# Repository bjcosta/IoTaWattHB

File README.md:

# IoTaWattHB
IoTaWatt Homebrew is a repository for experimentation with new ideas against the official IoTaWatt project developed by Bob Lemaire (https://github.com/boblemaire/IoTaWatt).

This repository brings all 3rd party dependencies required to build IoTaWatt into a single folder for simple archiving/backup using git submodules. The commands to manage the submodules may differ with your version of git

-------
Purpose

I am using this project as a means to experiment with electronic and embedded design. I dont expect all the things I am going to try will work out.

The IoTaWatt project works quite well as it is. However after playing with it a little, I decided I would like a few extra features and so this has given me a good project to run with. The main improvements I want to experiment with from base IotaWatt include:
* Add POST support for the pvoutput.org website
* Single voltage transformer for both powering the IoTaWatt and sampling the mains voltage
* Pulse monitoring for monitoring electrcial smart meters, gas and water mains
* Add push-button switch for manual interaction like resetting connected WiFi AP
* Use accurate V-ref as both a reference but also to provide the BIAS so software doesn't have to "guess" the DC offset
* Add support for temperature and humidity sensor
* Use more accurate sampling technique (simultaneous/continuous sampling)

A key problem that I came across in this work, is that the existing ESP8266 NodeMCU has very few available GPIO lines and IoTaWatt already uses them all.

A real solution for this problem is moving to an ESP32 based board. Based on his comments in forums, this is in the future plans for Bob. I wanted to have my changes work with close to stock IoTaWatt so if I choose in the future I can revert back to stock firmware. For this reason, I decided to try and creatively work around the GPIO limitation (inspired by official IoTaWatts usage of GPIO for the status LED) and keep using the ESP8266.

Building
--------

When building this project, I defined the following base locations. You can use whatever you like for these.

IOTAWATTHB_HOME=$HOME/dev/IoTaWattHB
ARDUINO_HOME=$IOTAWATTHB_HOME/arduino-1.8.5/

Checkout Source
---------------

First checkout the IoTaWattHB project
* mkdir $HOME/dev && cd $HOME/dev
* git clone ssh://git@github.com/bjcosta/IoTaWattHB.git

Then you need to pull in the 3rd party git submodules
* cd $IOTAWATTHB_HOME
* git submodule update --init --recursive

The repository uses a symlink to bring in Crypto library from arduinolibs. If you are building on windows, you will need to set up a manual junction:
** cd %IOTAWATTHB_HOME%\deps\libraries
** del Crypto
** mklink /j Crypto ..\arduinolibs\libraries\Crypto
** git update-index --assume-unchanged Crypto

Install Arduino IDE
-------------------

* https://www.arduino.cc/en/Main/Software (Used version 1.8.5)
* Extract the file to: ${ARDUINO_HOME}
** tar -xvJf arduino-1.8.5-linux64.tar.xz -C $IOTAWATTHB_HOME/
* cd ${ARDUINO_HOME} && ./arduino
* Change sketchbook location Menu: File -> Preferences
** Set Sketchbook location to: ${IOTAWATTHB_HOME}/deps
** I like to setup so that everything we depend on is in the projects folder so I can track versions for this project and return to it long in the future if I need to. Arduino is not great for this, but it is possible by changing your sketchbook location. Remember to restore it if you are working on other projects once you are finished with this one. 
** By doing this we can archive everything together (all 3rd party dependencies along with the module) and back it up.

Install ESP8266 dev tools
-------------------------

* http://esp8266.github.io/Arduino/versions/2.0.0/doc/installing.html
* The git submodule containing the dev tools has already been cloned under ${IOTAWATTHB_HOME}/deps/hardware/esp8266com/esp8266
* We still however need to download the necessary binaries for cross compiling
** cd ${IOTAWATTHB_HOME}/deps/hardware/esp8266com/esp8266/tools
** python get.py

Now compile the sketch
----------------------

* cd ${ARDUINO_HOME} && ./arduino
* Menu: File -> Open : ${IOTAWATTHB_HOME}/IoTaWatt/Firmware/IotaWatt/IotaWatt.ino
* Menu: Tools -> Board -> NodeMCU 1.0 (ESP-12E Module)
** Note: The 1.0 board is the one I was using, also known as 
* Menu: Sketch -> Verify/Compile

TODO
----

* Document setting up Exception decoder for Arduino ESP https://github.com/me-no-dev/EspExceptionDecoder
* Document setup of VisualMicro Visual Studio plugin http://www.visualmicro.com
* Document installation of FTDI drivers for Windows
** http://www.ftdichip.com/Drivers/VCP.htm
** http://www.ftdichip.com/Drivers/CDM/CDM%20v2.12.28%20WHQL%20Certified.zip
** http://www.ftdichip.com/Drivers/CDM/CDM21228_Setup.zip
* Document steps to upload and run a sketch

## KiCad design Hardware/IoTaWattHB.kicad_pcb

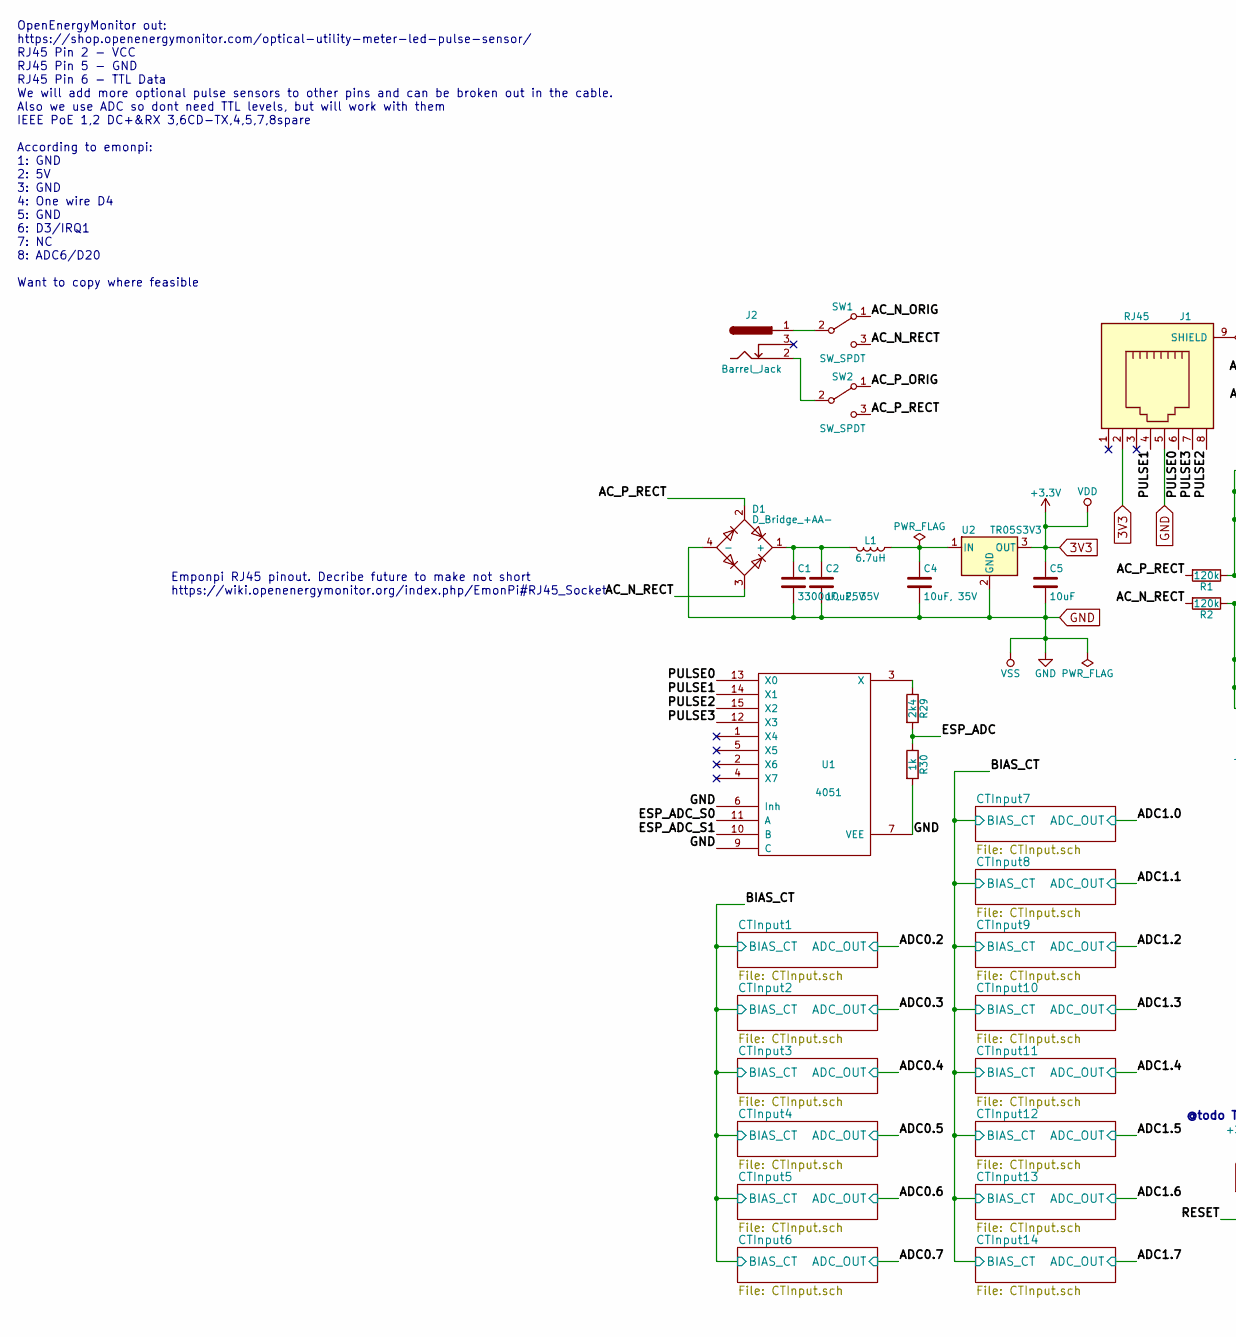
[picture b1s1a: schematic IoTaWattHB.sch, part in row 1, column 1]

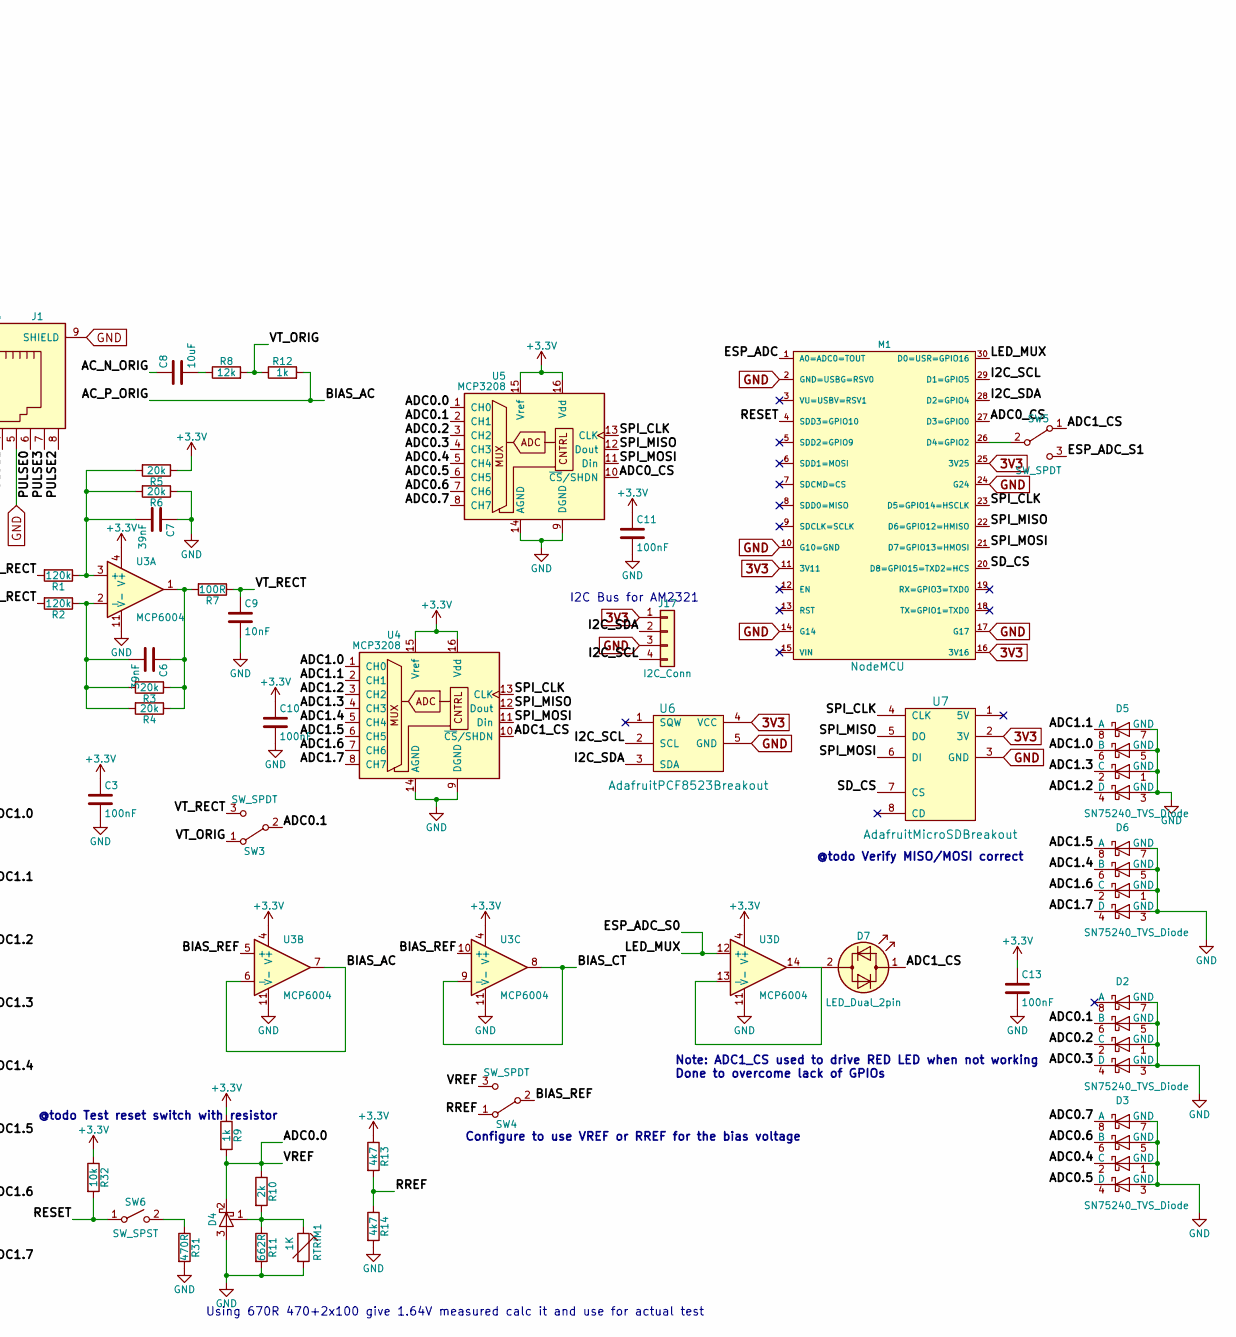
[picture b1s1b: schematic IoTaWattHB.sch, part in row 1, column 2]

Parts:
C1: 3300uF, 25V; CP_Radial_D16.0mm_P7.50mm
C2, C4: 10uF, 35V; CP_Radial_D5.0mm_P2.00mm
C3, C10, C11, C13: 100nF; C_Rect_L18.0mm_W5.0mm_P15.00mm_FKS3_FKP3
C5, C8: 10uF; CP_Radial_D5.0mm_P2.00mm
C6, C7: 39nF; C_Rect_L18.0mm_W5.0mm_P15.00mm_FKS3_FKP3
C9: 10nF; C_Disc_D12.5mm_W5.0mm_P7.50mm
D1: D_Bridge_+AA-; Diode_Bridge_14.5x3.5
D2, D3, D5, D6: SN75240_TVS_Diode; DIP-8_W7.62mm
D4: AdjustableShuntVoltageReference; TO-92_Inline_Narrow_Oval
D7: LED_Dual_2pin; LED_D5.0mm_Horizontal_O1.27mm_Z9.0mm
J1: RJ45; RJ45_TycoElectric_Side_8Pos
J2: Barrel_Jack; DC_RSPRO_2.1
J17: I2C_Conn; Socket_Strip_Straight_1x04_Pitch2.54mm
L1: 6.7uH; L_Axial_L16.0mm_D6.3mm_P7.62mm_Vertical_Fastron_VHBCC
M1: NodeMCU; NodeMCU_notracks
R1, R2: 120k; R_Axial_DIN0309_L9.0mm_D3.2mm_P15.24mm_Horizontal
R3, R4, R5, R6: 20k; R_Axial_DIN0309_L9.0mm_D3.2mm_P15.24mm_Horizontal
R7: 100R; R_Axial_DIN0309_L9.0mm_D3.2mm_P15.24mm_Horizontal
R8: 12k; R_Axial_DIN0309_L9.0mm_D3.2mm_P15.24mm_Horizontal
R9, R12, R30: 1k; R_Axial_DIN0309_L9.0mm_D3.2mm_P15.24mm_Horizontal
R10: 2k; R_Axial_DIN0309_L9.0mm_D3.2mm_P15.24mm_Horizontal
R11: 662R; R_Axial_DIN0309_L9.0mm_D3.2mm_P15.24mm_Horizontal
R13, R14: 4k7; R_Axial_DIN0309_L9.0mm_D3.2mm_P15.24mm_Horizontal
R29: 2k4; R_Axial_DIN0309_L9.0mm_D3.2mm_P15.24mm_Horizontal
R31: 470R; R_Axial_DIN0309_L9.0mm_D3.2mm_P15.24mm_Horizontal
R32: 10k; R_Axial_DIN0309_L9.0mm_D3.2mm_P15.24mm_Horizontal
RTRIM1: 1K; Potentiometer_Trimmer_ACP_CA9h5_Vertical_Px5.0mm_Py5.0mm
SW1, SW2, SW3, SW4, SW5: SW_SPDT; Pin_Header_Straight_1x03_Pitch2.54mm
SW6: SW_SPST; SW_SPST_Angled_9233WW
U1: 4051; DIP-16_W7.62mm
U2: TR05S3V3; TO-220-3_Vertical_or_SIP-3T
U3: MCP6004; DIP-14_W7.62mm
U4, U5: MCP3208; SOIC-16_ADAPTER_3.9x9.9mm_Pitch1.27mm_notracks
U6: AdafruitPCF8523Breakout
U7: AdafruitMicroSDBreakout

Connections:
3V3: C3.1, C5.1, C10.1, C11.1, C13.1, J1.2, J17.1, M1.11 (3V11), M1.16 (3V16), M1.25 (3V25), R5.1, R9.1, R13.1, R32.1, U1.16 (VDD), U2.3 (OUT), U3.4 (V+), U4.15 (Vref), U4.16 (Vdd), U5.15 (Vref), U5.16 (Vdd), U6.4 (VCC), U7.2 (3V)
/AC_N_ORIG: C8.1, SW1.1 (A)
/AC_N_RECT: D1.3, R2.2, SW1.3 (C)
/AC_P_ORIG: R12.2, SW2.1 (A), U3.6 (-), U3.7
/AC_P_RECT: D1.2, R1.2, SW2.3 (C)
/ADC0.0: D4.2 (K), R9.2, R10.1, SW4.3 (C), U5.1 (CH0)
/ADC0.1: D2.6 (B), SW3.2 (B), U5.2 (CH1)
/ADC0.2: D2.2 (C), U5.3 (CH2); also elsewhere on the board
/ADC0.3: D2.4 (D), U5.4 (CH3); also elsewhere on the board
/ADC0.4: D3.2 (C), U5.5 (CH4); also elsewhere on the board
/ADC0.5: D3.4 (D), U5.6 (CH5); also elsewhere on the board
/ADC0.6: D3.6 (B), U5.7 (CH6); also elsewhere on the board
/ADC0.7: D3.8 (A), U5.8 (CH7); also elsewhere on the board
/ADC0_CS: M1.27 (D3=GPIO0), U5.10 (~CS~/SHDN)
/ADC1.0: D5.6 (B), U4.1 (CH0); also elsewhere on the board
/ADC1.1: D5.8 (A), U4.2 (CH1); also elsewhere on the board
/ADC1.2: D5.4 (D), U4.3 (CH2); also elsewhere on the board
/ADC1.3: D5.2 (C), U4.4 (CH3); also elsewhere on the board
/ADC1.4: D6.6 (B), U4.5 (CH4); also elsewhere on the board
/ADC1.5: D6.8 (A), U4.6 (CH5); also elsewhere on the board
/ADC1.6: D6.2 (C), U4.7 (CH6); also elsewhere on the board
/ADC1.7: D6.4 (D), U4.8 (CH7); also elsewhere on the board
/ADC1_CS: D7.1 (KA), SW5.1 (A), U4.10 (~CS~/SHDN)
/BIAS_CT: U3.8, U3.9 (-); also elsewhere on the board
/BIAS_REF: SW4.2 (B), U3.5 (+), U3.10 (+)
/ESP_ADC: M1.1 (A0=ADC0=TOUT), R29.2, R30.1
/ESP_ADC_S0: M1.30 (D0=USR=GPIO16), U1.11 (A), U3.12 (+)
/ESP_ADC_S1: SW5.3 (C), U1.10 (B)
/I2C_SCL: J17.4, M1.29 (D1=GPIO5), U6.2 (SCL)
/I2C_SDA: J17.2, M1.28 (D2=GPIO4), U6.3 (SDA)
/PULSE0: J1.6, U1.13 (X0)
/PULSE1: J1.4, U1.14 (X1)
/PULSE2: J1.8, U1.15 (X2)
/PULSE3: J1.7, U1.12 (X3)
/RESET: M1.4 (SDD3=GPIO10), R32.2, SW6.1 (A)
/RREF: R13.2, R14.1, SW4.1 (A)
/SD_CS: M1.20 (D8=GPIO15=TXD2=HCS), U7.7 (CS)
/SPI_CLK: M1.23 (D5=GPIO14=HSCLK), U4.13 (CLK), U5.13 (CLK), U7.4 (CLK)
/SPI_MISO: M1.22 (D6=GPIO12=HMISO), U4.12 (Dout), U5.12 (Dout), U7.5 (DO)
/SPI_MOSI: M1.21 (D7=GPIO13=HMOSI), U4.11 (Din), U5.11 (Din), U7.6 (DI)
/VT_ORIG: R8.2, R12.1, SW3.1 (A)
/VT_RECT: C9.1, R7.1, SW3.3 (C)
GND: C1.2, C2.2, C3.2, C4.2, C5.2, C7.1, C9.2, C10.2, C11.2, C13.2, D1.4 (-), D2.1 (GND), D2.3 (GND), D2.5 (GND), D2.7 (GND), D3.1 (GND), D3.3 (GND), D3.5 (GND), D3.7 (GND), D4.3 (A), D5.1 (GND), D5.3 (GND), D5.5 (GND), D5.7 (GND), D6.1 (GND), D6.3 (GND), D6.5 (GND), D6.7 (GND), J1.5, J1.9 (SHIELD), J17.3, M1.2 (GND=USBG=RSV0), M1.10 (G10=GND), M1.14 (G14), M1.17 (G17), M1.24 (G24), R6.1, R11.2, R14.2, R30.2, R31.2, RTRIM1.2, U1.6 (Inh), U1.7 (VEE), U1.8 (VSS), U1.9 (C), U2.2 (GND), U3.11 (V-), U4.9 (DGND), U4.14 (AGND), U5.9 (DGND), U5.14 (AGND), U6.5 (GND), U7.3 (GND)
unnamed: C1.1, C2.1, D1.1 (+), L1.2
unnamed: C4.1, L1.1, U2.1 (IN)
unnamed: C6.1, R3.1, R4.1, R7.2, U3.1
unnamed: C6.2, R2.1, R3.2, R4.2, U3.2 (-)
unnamed: C7.2, R1.1, R5.2, R6.2, U3.3 (+)
unnamed: C8.2, R8.1
unnamed: D4.1 (FB), R10.2, R11.1, RTRIM1.1
unnamed: D7.2 (AK), U3.13 (-), U3.14
unnamed: J2.1, SW1.2 (B)
unnamed: J2.2, SW2.2 (B)
unnamed: M1.26 (D4=GPIO2), SW5.2 (B)
unnamed: R29.1, U1.3 (X)
unnamed: R31.1, SW6.2 (B)

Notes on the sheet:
@todo Verify MISO/MOSI correct
Note: ADC1_CS used to drive RED LED when not working Done to overcome lack of GPIOs
Configure to use VREF or RREF for the bias voltage
OpenEnergyMonitor out: https://shop.openenergymonitor.com/optical-utility-meter-led-pulse-sensor/ RJ45 Pin 2 - VCC RJ45 Pin 5 - GND RJ45 Pin 6 - TTL Data We will add more optional pulse sensors to other pins and can be broken out in the cable. Also we use ADC so dont need TTL levels, but will work 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
Using 670R 470+2x100 give 1.64V measured calc it and use for actual test
Emponpi RJ45 pinout. Decribe future to make not short https://wiki.openenergymonitor.org/index.php/EmonPi#RJ45_Socket
I2C Bus for AM2321
@todo Test reset switch with resistor

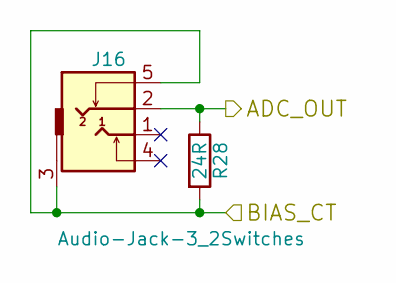
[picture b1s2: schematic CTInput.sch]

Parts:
J3: Audio-Jack-3_2Switches; Cliff_3.5mm_Stereo_TRS_2x_Switch_JY039-5P
R15: 24R; R_Axial_DIN0309_L9.0mm_D3.2mm_P15.24mm_Horizontal

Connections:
/ADC1.0: J3.2, R15.1; also elsewhere on the board
/BIAS_CT: J3.3, J3.5, R15.2; also elsewhere on the board

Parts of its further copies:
J4, J5, J6, J7, J8, J9, J10, J11, J12, J13, J14, J15, J16: Audio-Jack-3_2Switches; Cliff_3.5mm_Stereo_TRS_2x_Switch_JY039-5P
R16, R17, R18, R19, R20, R21, R22, R23, R24, R25, R26, R27, R28: 24R; R_Axial_DIN0309_L9.0mm_D3.2mm_P15.24mm_Horizontal

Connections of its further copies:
/ADC0.2: J4.2, R16.1; also elsewhere on the board
/ADC0.3: J5.2, R17.1; also elsewhere on the board
/ADC0.4: J6.2, R18.1; also elsewhere on the board
/ADC0.5: J7.2, R19.1; also elsewhere on the board
/ADC0.6: J8.2, R20.1; also elsewhere on the board
/ADC0.7: J9.2, R21.1; also elsewhere on the board
/ADC1.1: J16.2, R28.1; also elsewhere on the board
/ADC1.2: J10.2, R22.1; also elsewhere on the board
/ADC1.3: J11.2, R23.1; also elsewhere on the board
/ADC1.4: J12.2, R24.1; also elsewhere on the board
/ADC1.5: J13.2, R25.1; also elsewhere on the board
/ADC1.6: J14.2, R26.1; also elsewhere on the board
/ADC1.7: J15.2, R27.1; also elsewhere on the board
/BIAS_CT: J4.3, J4.5, J5.3, J5.5, J6.3, J6.5, J7.3, J7.5, J8.3, J8.5, J9.3, J9.5, J10.3, J10.5, J11.3, J11.5, J12.3, J12.5, J13.3, J13.5, J14.3, J14.5, J15.3, J15.5, J16.3, J16.5, R16.2, R17.2, R18.2, R19.2, R20.2, R21.2, R22.2, R23.2, R24.2, R25.2, R26.2, R27.2, R28.2; also elsewhere on the board

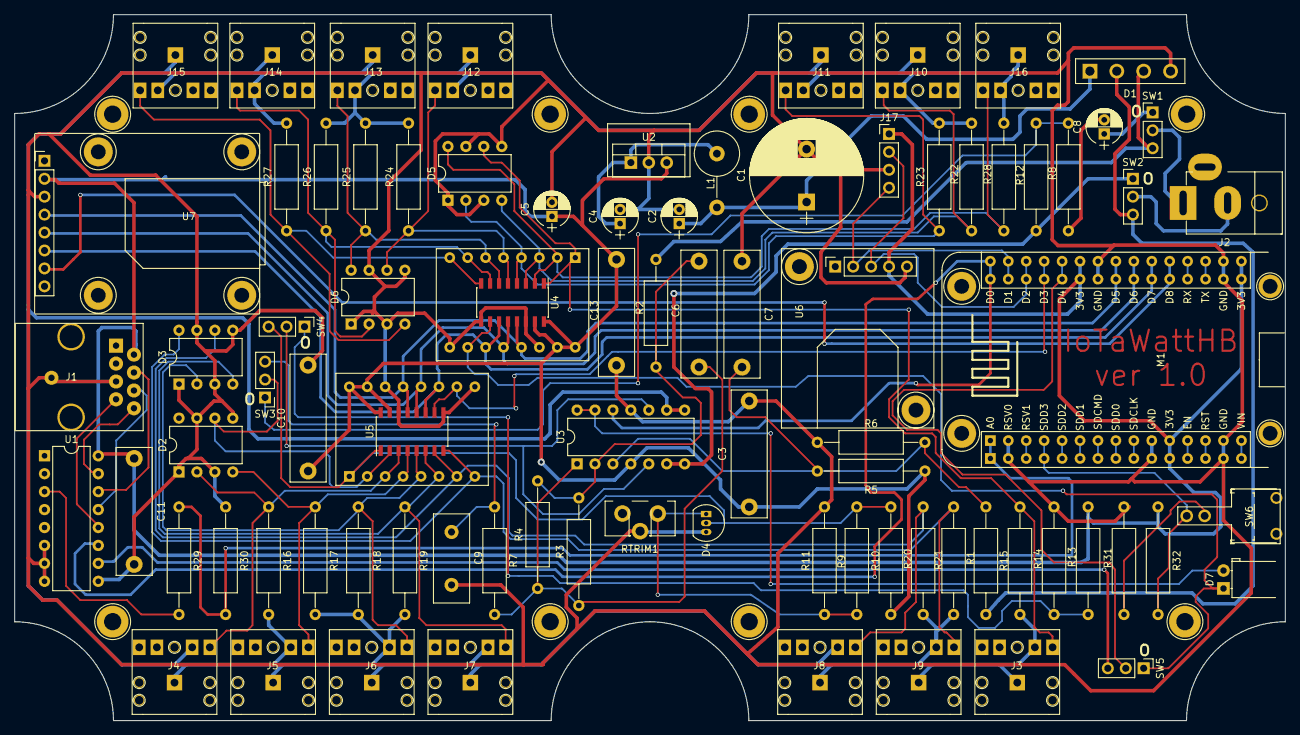
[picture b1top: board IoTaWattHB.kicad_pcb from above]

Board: 2 copper layers, 180.0 x 100.0 mm, 92 parts (0 on the bottom side), 56 nets.

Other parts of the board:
MOUNT5, MOUNT5#2, MOUNT5#3, MOUNT5#4, MOUNT5#5, MOUNT5#6, MOUNT5#7, MOUNT5#8: MountingHoleM2Panhead; MountingHole2.0mm

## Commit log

2017-10-30 Added IoTaWatt subdirectory for project
2017-10-30 Added 3rd part dependencies
2017-10-30 Moved arduinolibs so I can create a symlink for individual libraries
2017-10-30 More fixes for broken submodule
2017-10-30 Weird removed from gitmodules. Will re-add
2017-10-30 Added arduinolibs again
2017-10-30 Added symlink for crypto to submodule
2017-10-30 Added visual studio project files for building IoTaWatt with Visual Micro plugin for visual studio
2017-10-30 Added Crypto symlink to the ignore list
2017-10-30 Added todo file and config I use for my hacked up hardware on a breadboard
2017-10-30 Updated to point to pvoutput branch
2017-10-30 Added initial pvoutput support
2017-11-01 Updated clang format and added initial readme
2017-12-21 Initial IoTaWattHB hardware board designed and sent for manufacture
2017-12-22 Started updating the documentation of the work log
